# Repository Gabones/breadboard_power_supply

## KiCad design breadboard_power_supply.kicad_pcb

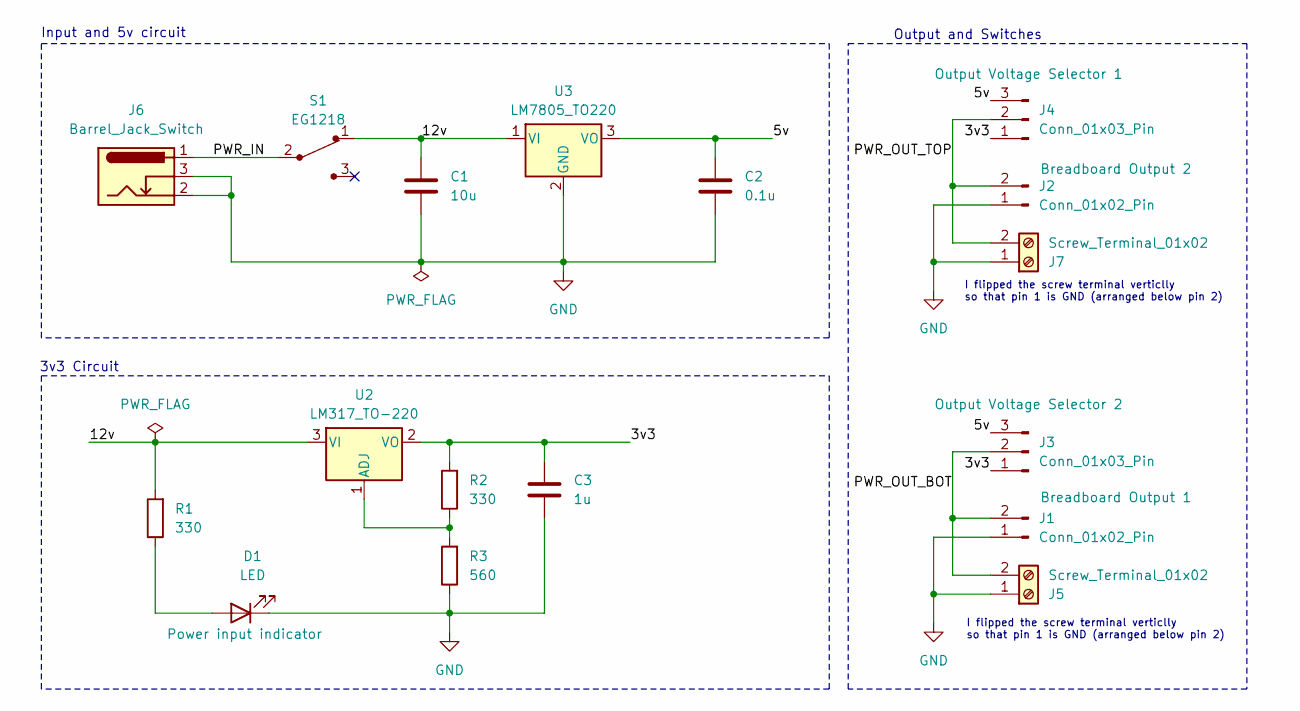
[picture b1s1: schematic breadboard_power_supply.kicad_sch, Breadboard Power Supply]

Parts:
C1: 10u; C_Disc_D3.0mm_W1.6mm_P2.50mm
C2: 0.1u; C_Disc_D3.0mm_W1.6mm_P2.50mm
C3: 1u; C_Disc_D3.0mm_W1.6mm_P2.50mm
D1: LED; LED_D5.0mm
J1, J2: Conn_01x02_Pin; PinHeader_1x02_P2.54mm_Vertical
J3, J4: Conn_01x03_Pin; PinHeader_1x03_P2.54mm_Vertical
J5, J7: Screw_Terminal_01x02; TerminalBlock_bornier-2_P5.08mm
J6: Barrel_Jack_Switch; BarrelJack_Horizontal
R1, R2: 330; R_Axial_DIN0204_L3.6mm_D1.6mm_P7.62mm_Horizontal
R3: 560; R_Axial_DIN0204_L3.6mm_D1.6mm_P7.62mm_Horizontal
S1: EG1218; Switch_Slide_11.6x4mm_EG1218; MPN EG1218
U2: LM317_TO-220; TO-220-3_Vertical
U3: LM7805_TO220; TO-220-3_Vertical

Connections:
/3v3: C3.1, J3.1, J4.1, R2.2, U2.2 (VO)
/5v: C2.1, J3.3, J4.3, U3.3 (VO)
/12v: C1.1, R1.2, S1.1, U2.3 (VI), U3.1 (VI)
/PWR_IN: J6.1, S1.2
/PWR_OUT_BOT: J1.2, J3.2, J5.2
/PWR_OUT_TOP: J2.2, J4.2, J7.2
GND: C1.2, C2.2, C3.2, D1.1 (K), J1.1, J2.1, J5.1, J6.2, J6.3, J7.1, R3.1, U3.2 (GND)
unnamed: D1.2 (A), R1.1
unnamed: R2.1, R3.2, U2.1 (ADJ)

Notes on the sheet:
Output and Switches
3v3 Circuit
I flipped the screw terminal verticlly so that pin 1 is GND (arranged below pin 2)
Input and 5v circuit

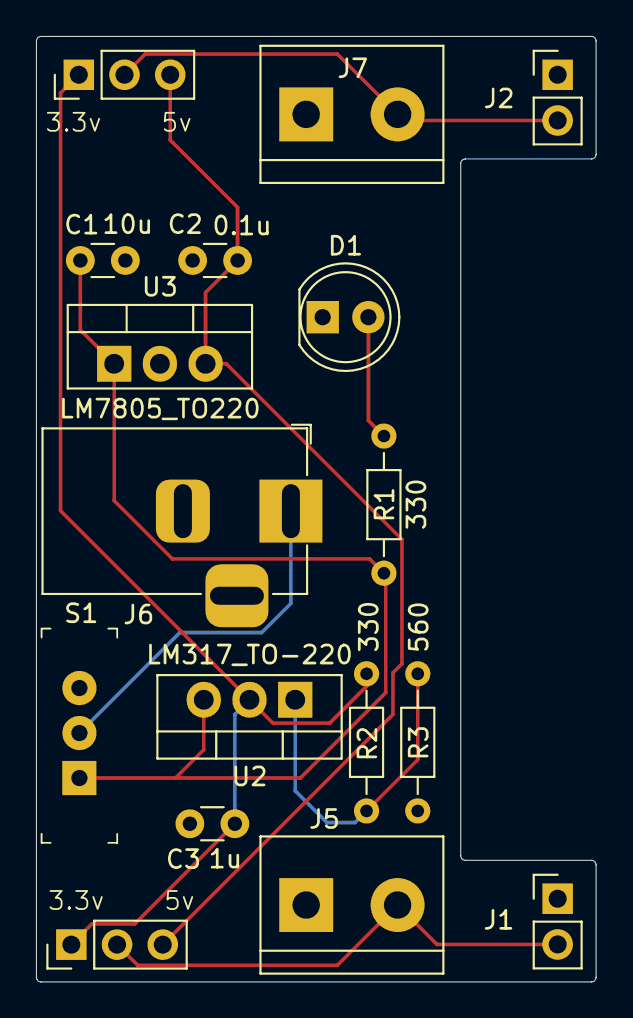
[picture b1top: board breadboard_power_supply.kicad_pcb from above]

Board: 2 copper layers, 31.1 x 52.5 mm, 17 parts (0 on the bottom side), 9 nets.

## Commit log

2024-03-25 v0.1
